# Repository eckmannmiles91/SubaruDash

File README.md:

# SubaruDash

Digital dash project for 2013 Subaru WRX

## Overview

This project documents the development of a custom digital dashboard for a 2013 WRX, including cluster EEPROM backup/modification work.

## Documentation

- [CLUSTER_EEPROM_GUIDE.md](CLUSTER_EEPROM_GUIDE.md) - Guide for reading and writing the instrument cluster EEPROM using CH341A programmer
- [CAN_SNIFFING_GUIDE.md](CAN_SNIFFING_GUIDE.md) - Guide for CAN bus sniffing using Raspberry Pi 5 and MCP2515 module
- [CUSTOM_PCB_DESIGN.md](CUSTOM_PCB_DESIGN.md) - Custom "WRX Power & CAN HAT" PCB design specification

## Tools

- [tools/AsProgrammer/](tools/AsProgrammer/) - AsProgrammer v2.1.2 for reading/writing EEPROM chips (Windows)

## Hardware

### Cluster EEPROM Work
- CH341A USB EEPROM Programmer - [Amazon Link](https://www.amazon.com/dp/B07VNVVXW6)
- 2013 WRX backup instrument cluster (eBay)

### CAN Bus Sniffing
- Raspberry Pi 5 with OpenDash installed
- 2x MCP2515 CAN Bus Module (TJA1050 transceiver)
- OBD-II Splitter Cable
- 12V to 5V buck converter
- Jumper wires

## Current Status

### Cluster EEPROM Work
- [ ] Backup cluster received (ordered from eBay)
- [x] EEPROM chip identified (S93C76)
- [x] Main MCU identified (MB90428GAV)
- [x] CH341A programmer purchased and set up
- [x] Documentation created for EEPROM reading/writing
- [ ] Backup cluster EEPROM read and backed up

### CAN Bus Sniffing
- [x] MCP2515 CAN modules available (2x)
- [x] Raspberry Pi 5 with OpenDash running
- [x] OBD-II splitter cable available
- [x] CAN sniffing documentation created
- [ ] MCP2515 connected to Pi5 GPIO
- [ ] SocketCAN configured on Pi5
- [ ] CAN bus data collection started
- [ ] CAN IDs mapped for WRX sensors

### Digital Dash Development
- [ ] Hardware platform selection
- [ ] Display selection
- [ ] Software architecture design
- [ ] Implementation

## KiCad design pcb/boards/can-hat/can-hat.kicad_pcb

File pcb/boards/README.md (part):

# SubaruDash Split Board Schematics

This directory contains the split schematics from the combined `wrx-power-can-hat-MANUAL.kicad_sch` into three separate stackable Raspberry Pi HAT boards.

## Board Structure

### 1. Power HAT (`power-hat/`)
**Schematic Status: ✅ ERC CLEAN - 0 Errors, 55 Warnings**
**PCB Status: 🟡 Layout v6 Ready - J1 updated to Micro-Fit 3.0 6-pin**

Core power management and ignition control:
- **U1**: TPS54560 5V/5A Buck Converter (12V → 5V)
- **U3**: ATtiny85 Power Management MCU
- **J1**: 12V Input Molex Micro-Fit 3.0 (6-pin)
- **J2**: 40-pin Raspberry Pi GPIO Header
- **J4**: 4-pin PWM Fan Connector (30mm fan)
- **F1**: Input Fuse
- MOSFETs (Q1, Q2, Q3) for power switching
- Ignition detection optocoupler circuit

**Connected Signals via Pi Header:** (see [GPIO_ALLOCATION.md](GPIO_ALLOCATION.md))
- +5V (pins 2, 4)
- +3.3V (pins 1, 17)
- GND (pins 6, 9, 14, 20, 25, 30, 34, 39)
- SHUTDOWN_REQ (pin 7/GPIO4) - Pi → ATtiny85 shutdown request
- HEARTBEAT_LED (pin 11/GPIO17) - ATtiny85 → Pi heartbeat status
- TIMER_LED (pin 13/GPIO27) - ATtiny85 → Pi timer status
- IGN_DETECT (pin 15/GPIO22) - Optocoupler → Pi ignition state
- FAN_PWM (pin 32/GPIO12) - Pi → Fan PWM speed control
- FAN_TACH (pin 33/GPIO13) - Fan → Pi tachometer feedback

**PCB Layout Features:**
- Board outline: 65mm × 56mm (standard Pi HAT)
- 4× M2.5 HAT mounting holes at corners (3.5, 3.5), (61.5, 3.5), (3.5, 52.5), (61.5, 52.5)
- 4× M3 fan mounting holes for 30mm fan (24mm spacing) centered at (32.5, 32)
- 40-pin GPIO header (J2) horizontal along top edge
- Power section (U1, L1) on left side, clear of fan zone
- MCU section (U3, Y1) on right side
- Power switching (Q1) bottom-right
- Layout scripts: `layout_power_hat_v5.py` (optimized), `layout_power_hat_v6.py` (DRC-compliant)

**Two-Layer Component Strategy:**
- **Front layer (F.Cu):** Through-hole and thermal components
  - Connectors: J1, J2, J3, J4, JP1, JP2
  - ICs: U1 (TPS54560), U2 (optocoupler), U3 (ATtiny85)
  - Power: Q1 (TO-220 MOSFET), L1 (inductor), F1 (fuse)
  - Crystal: Y1
- **Back layer (B.Cu):** SMD passives positioned under related front components
  - Under U1 (buck converter): R1, R2, R_RT1, R_COMP1, D2
  - Under U3 (MCU): R4, R5, R6, R7
  - Under U2 (optocoupler): R8, R9
  - Under Q1 (MOSFET): Q2, Q3, R10
  - Under J1 (power input): D1
  - Capacitors: C1-C9, C_BOOT1, C_COMP1

### 2. CAN HAT (`can-hat/`)
**Schematic Status: ✅ ERC CLEAN - Fixed crystal, OBD-II, and power connections**
**PCB Status: ⏳ Not Started**

CAN bus communication interface:
- **U2**: MCP2515 CAN Controller (SPI interface)
- **U3**: SN65HVD230 CAN Transceiver (3.3V native)
- **U1**: AMS1117-3.3 Voltage Regulator
- **J1**: 40-pin Raspberry Pi GPIO Header
- **J2**: OBD-II 16-pin Connector
- **J3**: CAN Screw Terminal
- **Y1**: 8MHz Crystal

**Connected Signals via Pi Header:** (see [GPIO_ALLOCATION.md](GPIO_ALLOCATION.md))
- +5V (pins 2, 4) - power input (stacking or USB-C)
- +3.3V (pins 1, 17) - from AMS1117
- GND (pins 6, 9, 14, 20, 25, 30, 34, 39)
- SPI_MOSI (pin 19/GPIO10)
- SPI_MISO (pin 21/GPIO9)
- SPI_SCLK (pin 23/GPIO11)
- SPI_CE0 (pin 24/GPIO8)
- CAN_INT (pin 22/GPIO25)

**USB-C Power Input (Manual Addition Required):**
- J5: USB-C connector for bench testing
- D1, D2: SS34 Schottky diodes (power OR'ing)
- Allows power from either GPIO header or USB-C

### 3. DAC/Amp HAT (`dac-amp/`)
**Schematic Status: ✅ ERC CLEAN - 34 Errors (J7 GPIO only), 85 Warnings**
**PCB Status: ✅ READY FOR PCBA - DRC clean, Gerbers generated**

4-channel 50W Class D audio amplifier:
- **U1**: PCM5142 Stereo I2S DAC
- **U2**: AMS1117-3.3 LDO (3.3V for DAC)
- **U3**: TPA3116D2DAD Class D Amplifier (Front L/R, 50W stereo BTL)
- **U4**: TPA3116D2DAD Class D Amplifier (Rear L/R, 50W stereo BTL)
- **J3**: 4-pin 3.5mm screw terminal (Front speakers: FL+, FL-, FR+, FR-)
- **J4**: 4-pin 3.5mm screw terminal (Rear speakers: RL+, RL-, RR+, RR-)
- **J7**: 40-pin Raspberry Pi GPIO Header

**Support Components Added:**
- R1, R2: 4.7kΩ I2C pull-ups (SCL, SDA to +3.3V)
- C4-C6: PCM5142 decoupling (100nF DVDD, 100nF+10µF AVDD)
- C7-C10: TPA3116D2 bootstrap caps (100nF each, BSPx↔BSNx)
- C11-C20: TPA3116D2 PVCC decoupling (8× 100nF + 2× 10µF)
- C21-C22: TPA3116D2 GVDD decoupling (100nF each)
- C23-C30: Input coupling caps (1µF each, AC coupling to amp inputs)
- C31: 12V input bulk capacitor (100µF)
- C32: 3.3V filter capacitor (100nF)

**Connected Signals via Pi Header (J7):**
- +5V (pins 2, 4) - power input
- +3.3V (pins 1, 17) - from AMS1117
- GND (pins 6, 9, 14, 20, 25, 30, 34, 39)
- I2S_BCK (pin 12/GPIO18) - I2S bit clock
- I2S_LRCK (pin 35/GPIO19) - I2S L/R clock
- I2S_DOUT (pin 40/GPIO21) - I2S data out
- I2C_SDA (pin 3/GPIO2) - PCM5142 config
- I2C_SCL (pin 5/GPIO3) - PCM5142 config

**Volume Control:** Digital via PCM5142 I2C registers (not analog PLIMIT)

**PCB Layout Features:**
- Board outline: 65mm × 56mm (standard Pi HAT)
- 4× M2.5 HAT mounting holes at standard positions
- 2-layer board, routed via FreeRouting auto-router
- GND copper pour on back layer for thermal dissipation
- Thermal vias under U3 and U4 (6-8 vias each)
- Widened power traces: +12V @ 1.0mm, speaker outputs @ 0.75mm
- 3× fiducials for pick-and-place assembly
- Components on both front and back layers

**Manufacturing Recommendations:**
- Copper weight: 2oz preferred (1oz acceptable for prototypes)
- Surface finish: ENIG (for PCBA) or HASL lead-free
- Assembly: PCBA recommended (TPA3116D2 and PCM5142 are SMD with fine pitch)

## Scripts

| Script | Purpose |
|--------|---------|
| `split_schematic.py` | Initial split of combined schematic |
| `cleanup_schematics.py` | Remove cross-board labels |
| `fix_power_hat.py` | Remove CAN-specific labels from Power HAT |
| `fix_power_hat_complete.py` | (v1) Wire J2 pins - had position errors |
| `fix_power_hat_v2.py` | (v2) Wire J2 pins with CORRECT positions |
| `fix_power_hat_v3.py` | Add PWR_FLAG symbols for power nets |
| `fix_power_hat_v4.py` | Connect J1, F1, U1 VIN, U3 VCC |
| `fix_power_hat_v5.py` | Connect remaining components (Q1, R5-R10, Y1, J3, JP1-2) |
| `fix_power_hat_v6.py` | Final fixes: PWR_FLAG for U1, R6/Y1/R10/Q3 connections |
| `fix_power_hat_v7.py` | Restore R6 connections (12V_IGN, GND) after cleanup |
| `fix_power_hat_v8.py` | Fix Y1 Pin 1 -> XTAL1 connection |
| `fix_power_hat_v9.py` | Bridge wire for Y1 Pin 1 gap |
| `fix_power_hat_v10.py` | T-junction approach for Y1 |
| `fix_power_hat_v11.py` | Stub wire at Y1 Pin 1 (+ manual snap to pin) |
| `fix_power_hat_v12.py` | Remove orphan HEARTBEAT_LED/TIMER_LED labels |
| `fix_power_hat_v13.py` | Add no_connect for U3 pins 5,6 (superseded by v14) |
| `fix_power_hat_v14.py` | Wire U3 PB0/PB1 to GPIO17/GPIO27 for status signals |
| `fix_can_hat.py` | Complete CAN HAT wiring (GPIO, SPI, CAN, power) |
| `create_dac_amp_schematic.py` | Generate DAC/Amp schematic from scratch |
| `layout_power_hat.py` | Power HAT PCB component placement |
| `layout_power_hat_v2.py` | Improved layout with better spacing |
| `layout_power_hat_v3.py` | X735-style layout with 30mm fan |
| `fix_power_hat_fan.py` | Upgrade J4 from 2-pin to 4-pin fan connector |
| `fix_power_hat_fan_complete.py` | Wire J4 pins 3,4 to GPIO12,13 for PWM fan control |
| `layout_power_hat_v4.py` | Improved layout with fan clearance zones |
| `move_caps_to_back.py` | Move capacitors to B.Cu (back layer) |
| `fix_cap_pads.py` | Fix SMD pad layers for back-layer components |
| `move_smd_to_back.py` | Move resistors, diodes, SOT-23 MOSFETs to B.Cu |
| `fix_back_positions.py` | Apply board offset to back-layer component positions |
| `fix_boot_comp_caps.py` | Move C_BOOT1/C_COMP1 to B.Cu (back layer) |
| `layout_power_hat_v5.py` | Optimized layout with all components positioned |
| `layout_power_hat_v6.py` | DRC-compliant spacing, J1 Micro-Fit 3.0 support |

## Current ERC Status

### Power HAT
After running fix scripts v2 through v5:
- ✅ J2 Pi header 40 pins connected (v2)
- ✅ PWR_FLAG symbols added for +5V, +3.3V, GND (v3)
- ✅ J1 12V input connector connected (v4)
- ✅ F1 fuse output -> 12V_FUSED (v4)
- ✅ U1 VIN -> 12V_FUSED (v4)
- ✅ U3 VCC -> +5V (v4)
- ✅ TPS54560 compensation network (C_COMP1, R_RT1) (v5)
- ✅ Power switching circuit (Q1, R5, R6, R8) (v5)
- ✅ Crystal oscillator Y1 -> XTAL1/XTAL2 (v5)
- ✅ J3, JP1, JP2 headers marked as no-connect (v5)
- ✅ R10 LED resistor -> GND (v5)
- ✅ J4 fan connector -> FAN+ (v5)
- ✅ PWR_FLAG on 12V_FUSED net (v6) - fixes U1 VIN power error
- ✅ R6 Pin 1 -> 12V_IGN (v6)
- ✅ Y1 Pin 1 -> XTAL1 (v6)
- ✅ Q3 Gate -> FAN_PWM (v6)
- ✅ R6 Pin 1 -> 12V_IGN, Pin 2 -> GND restored (v7)
- ✅ Y1 Pin 1 -> XTAL1 (v8-v11 + manual fix)
- ✅ Orphan labels deleted manually
- ✅ U3 PB0 (HEARTBEAT_LED) -> J2 Pin 11 (GPIO17) (v14)
- ✅ U3 PB1 (TIMER_LED) -> J2 Pin 13 (GPIO27) (v14)
- ✅ J1 updated to Molex Micro-Fit 3.0 6-pin (manual)
- ✅ C6 fixed: bottom pin changed from +3.3V to GND (was shorted)
- ✅ C8 reconnected as feedforward cap: +5V to U1-FB (was incorrectly on XTAL2)
- ✅ C9 label fixed: 12V_FUSED (was 12V_IGN)
- ✅ R6 label fixed: 12V_IGN to GND (ignition detection divider)
- ✅ D1 (TVS) moved away from J2, reconnected: 12V_FUSED to GND
- ✅ Removed stray 12V_IGN label hidden behind U1
- ✅ PWR_FLAG added to 12V_FUSED and +3.3V nets
- ✅ **ERC: 0 ERRORS, 55 WARNINGS** (warnings are non-critical)

### CAN HAT
After running fix_can_hat.py:
- ✅ J1 Pi header 40 pins connected with labels
- ✅ SPI bus: MOSI, MISO, SCLK, CE0 to MCP2515
- ✅ CAN_INT from MCP2515 to GPIO25
- ✅ MCP2515 to SN65HVD230 (CAN_TX, CAN_RX)
- ✅ Crystal Y1 connected (XTAL1, XTAL2)
- ✅ CAN bus to J2 (OBD-II) pins 6, 14
- ✅ CAN bus to J3 (screw terminal)
- ✅ Power distribution (AMS1117 5V_BUS -> +3.3V)
- ✅ PWR_FLAG symbols for +5V, +3.3V, GND
- ✅ Unused GPIO pins marked no-connect
- ✅ Unused OBD-II pins marked no-connect
- ⏳ USB-C power circuit components need manual addition
- ⚠️ Run ERC in KiCad to check remaining errors

### DAC/Amp
After manual wiring in KiCad:
- ✅ I2C pull-ups (R1, R2) wired to +3.3V and I2C_SCL/SDA labels
- ✅ PCM5142 decoupling (C4-C6) wired to +3.3V and GND
- ✅ Bootstrap caps (C7-C10) wired BSPx↔BSNx (NOT to outputs)
- ✅ PVCC decoupling (C11-C20) wired to +12V and GND
- ✅ GVDD decoupling (C21-C22) wired with PWR_FLAG (internal 5.2V)
- ✅ Input coupling (C23-C30) wired in series with amp inputs
- ✅ Power filtering (C31, C32) wired to +12V/+3.3V and GND
- ✅ Speaker outputs (J3, J4) wired to U3/U4 OUTP/OUTN pins
- ✅ PWR_FLAG added to +12V and GND nets
- ✅ **ERC: 34 ERRORS (all J7 GPIO unconnected - expected), 85 WARNINGS**

## GPIO Pin Allocation

See **[GPIO_ALLOCATION.md](GPIO_ALLOCATION.md)** for the complete GPIO pin mapping across all three HAT boards. This document tracks:
- Which GPIO pins are used by each board
- Signal directions and descriptions
- Available GPIOs for future expansion

## Technical Notes

### Conn_02x20_Odd_Even Pin Positions
The Raspberry Pi GPIO header uses specific pin offsets:
- **Odd pins (left)**: x = symbol_x - 5.08mm
- **Even pins (right)**: x = symbol_x + 7.62mm
- **Y spacing**: 2.54mm per row, starting at y_offset = 22.86mm

For J2 at position (200, 150):
- Pin 1: (194.92, 127.14)
- Pin 2: (207.62, 127.14)
- Pin 3: (194.92, 129.68)
- etc.

### Power Flow
```
12V_IGN (vehicle) → F1 (fuse) → 12V_FUSED
                                    ↓
                               U1 TPS54560
                                    ↓
                                  +5V → Pi Header, CAN HAT
                                    ↓
                               U3 LDO (on CAN HAT or Power HAT)
                                    ↓
                                 +3.3V → MCUs, DAC
```

## Next Steps

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
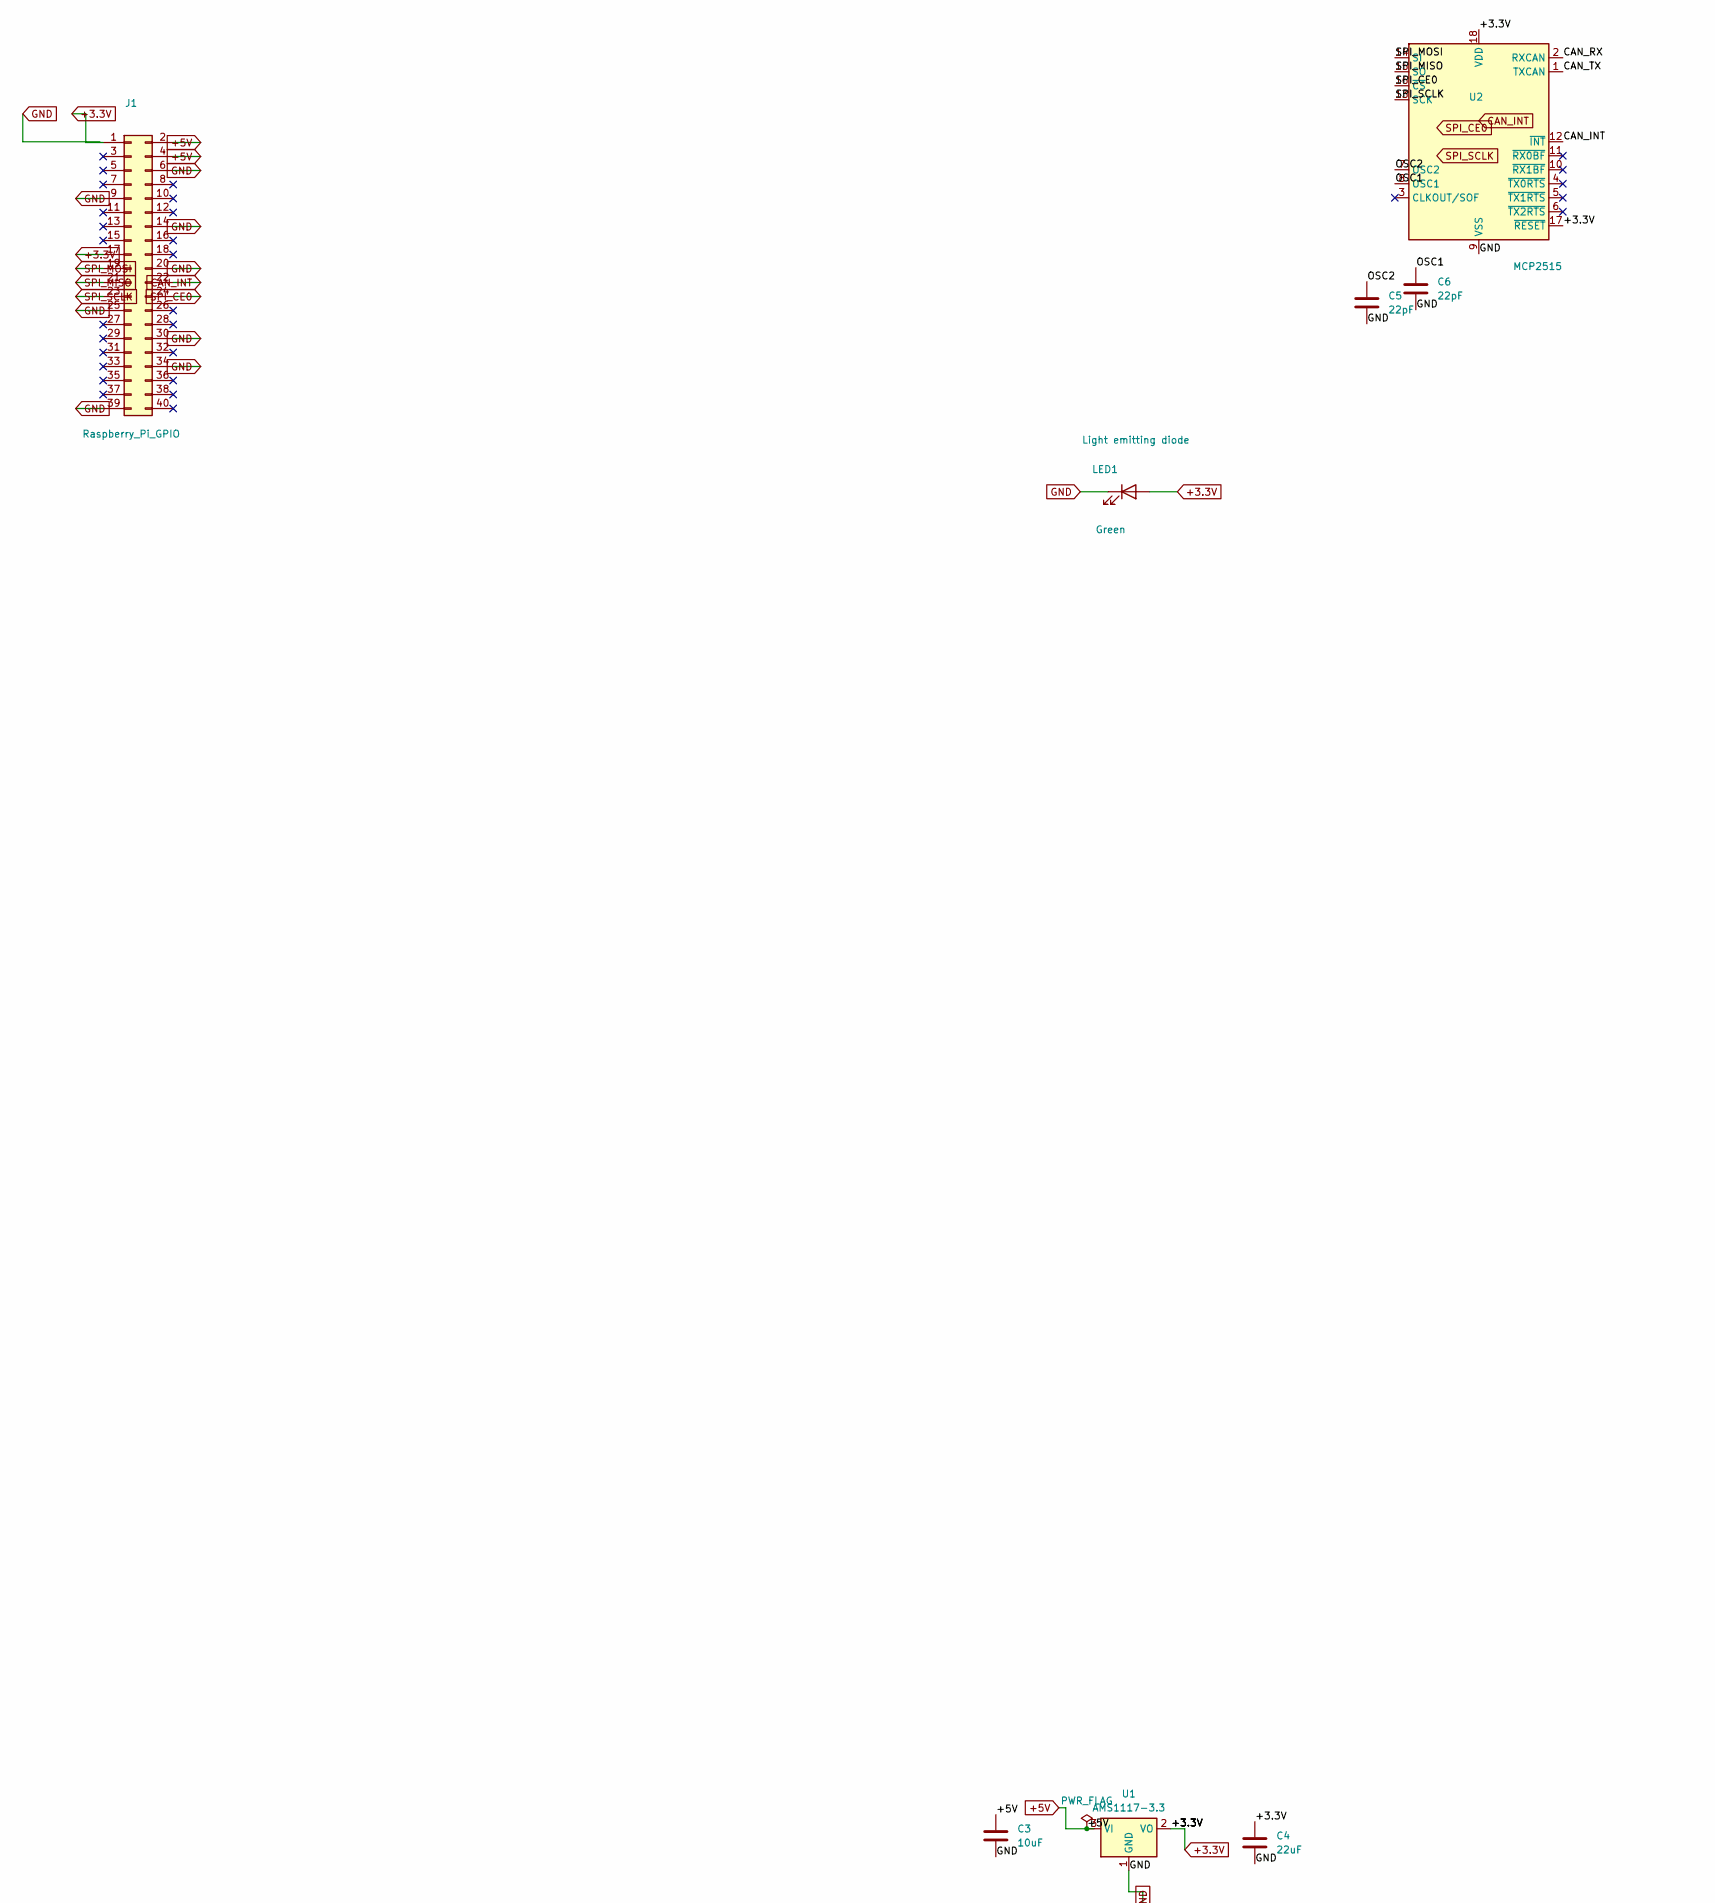
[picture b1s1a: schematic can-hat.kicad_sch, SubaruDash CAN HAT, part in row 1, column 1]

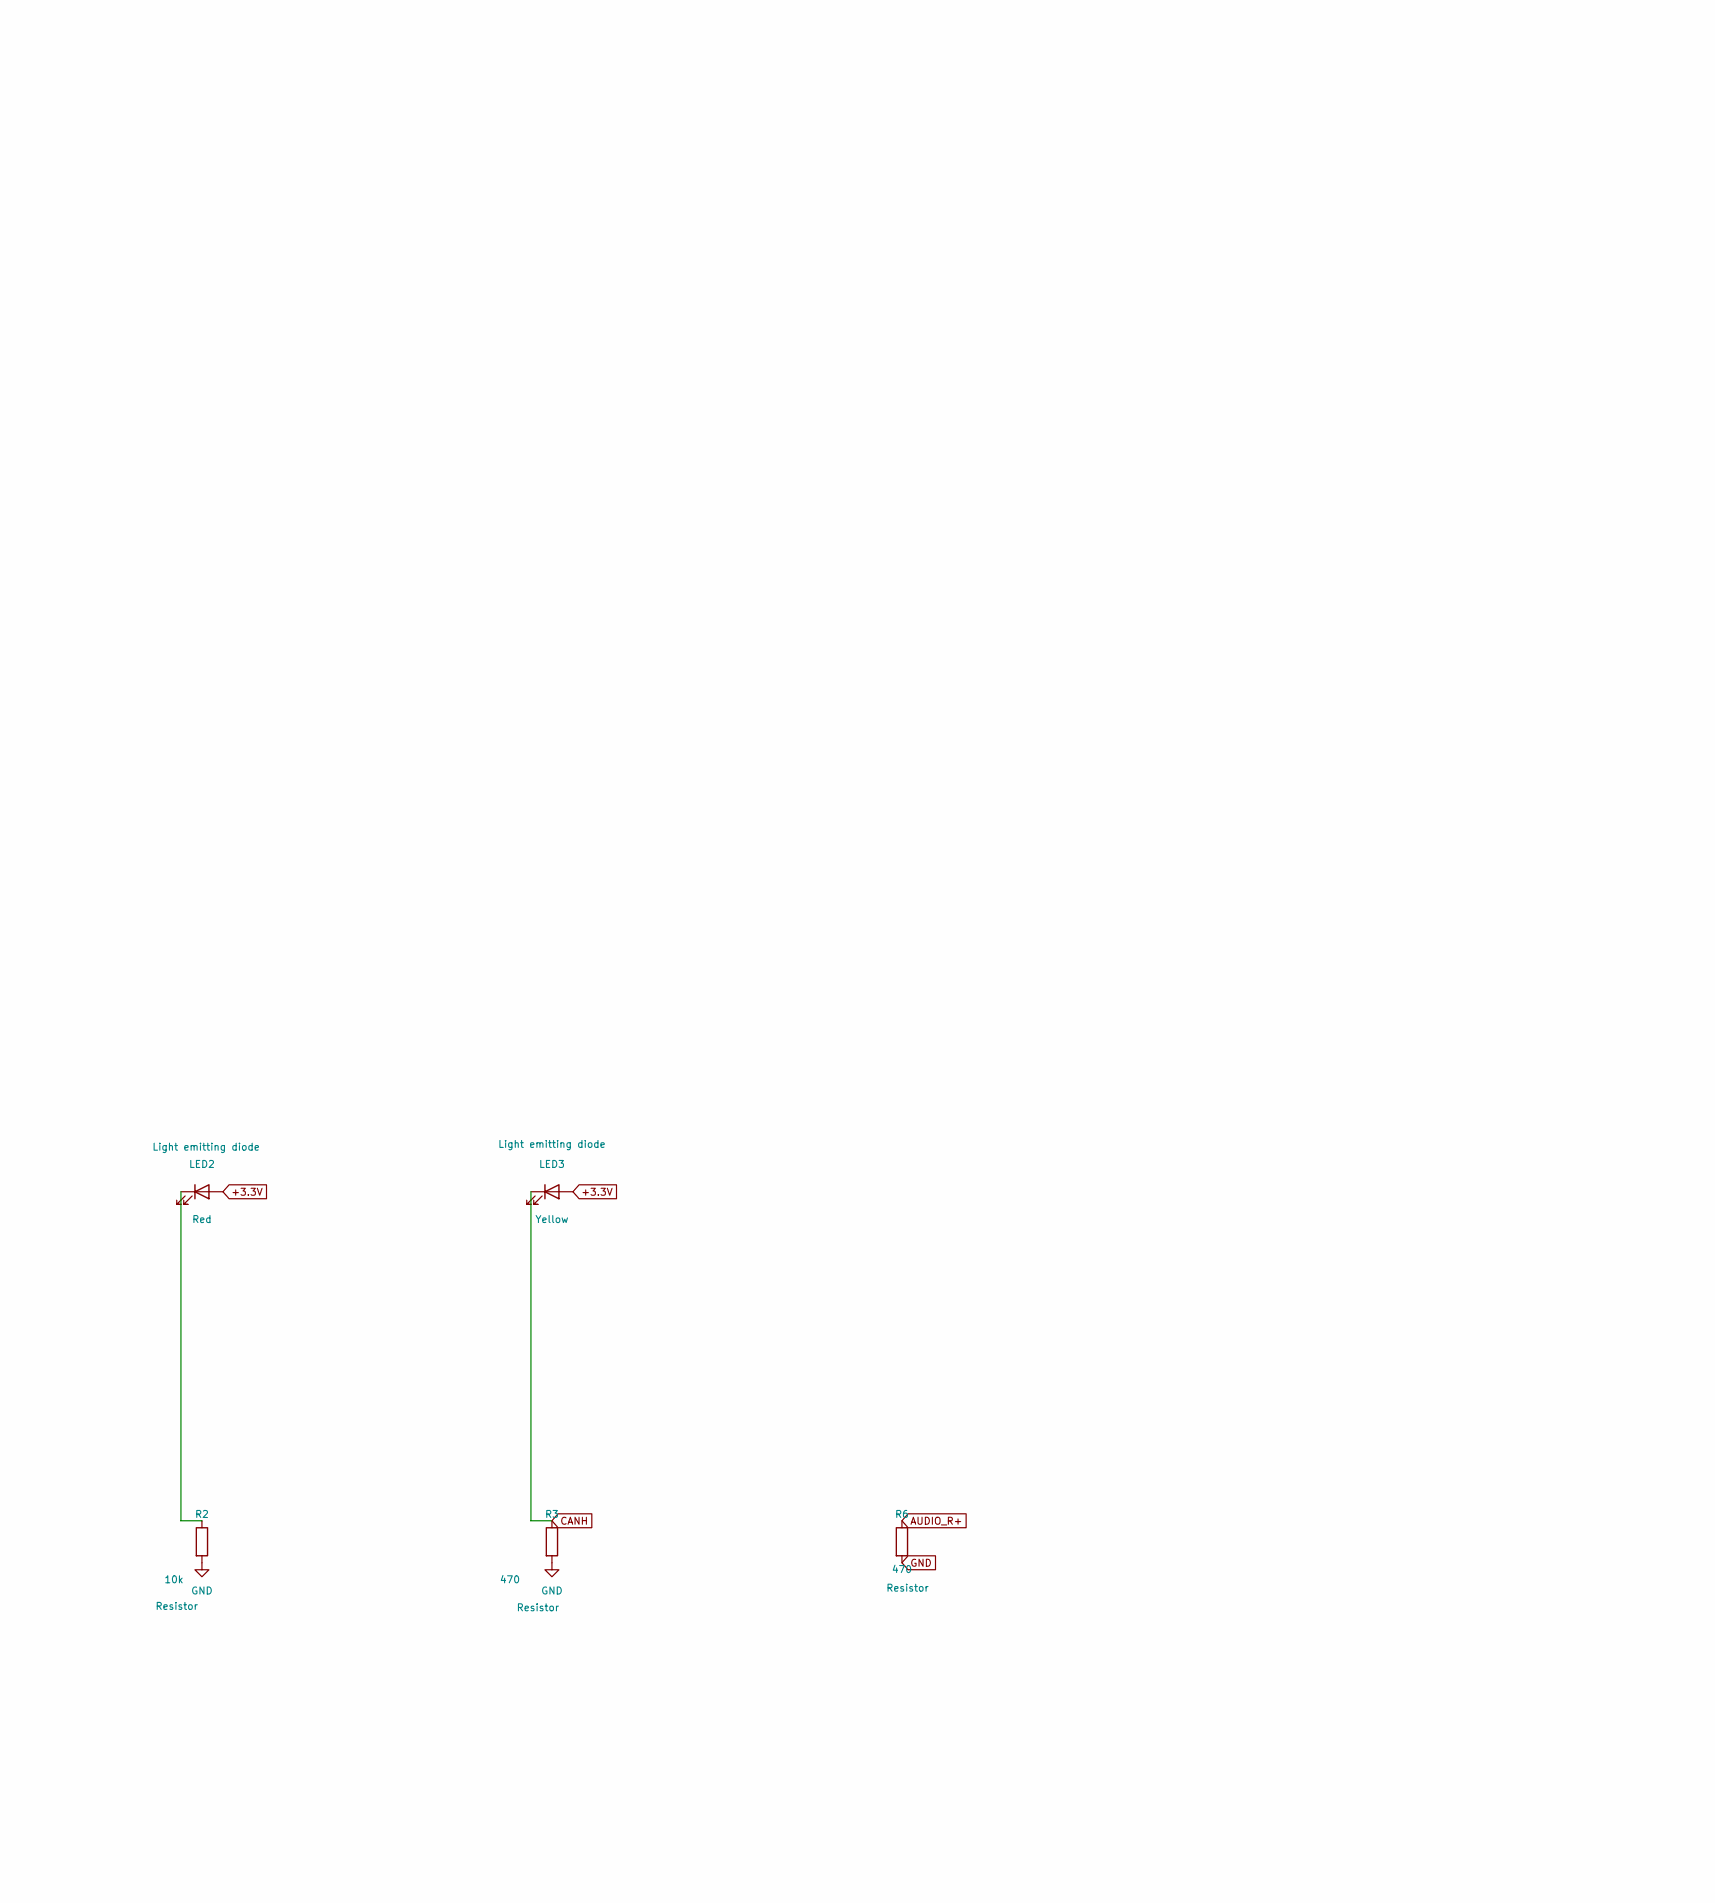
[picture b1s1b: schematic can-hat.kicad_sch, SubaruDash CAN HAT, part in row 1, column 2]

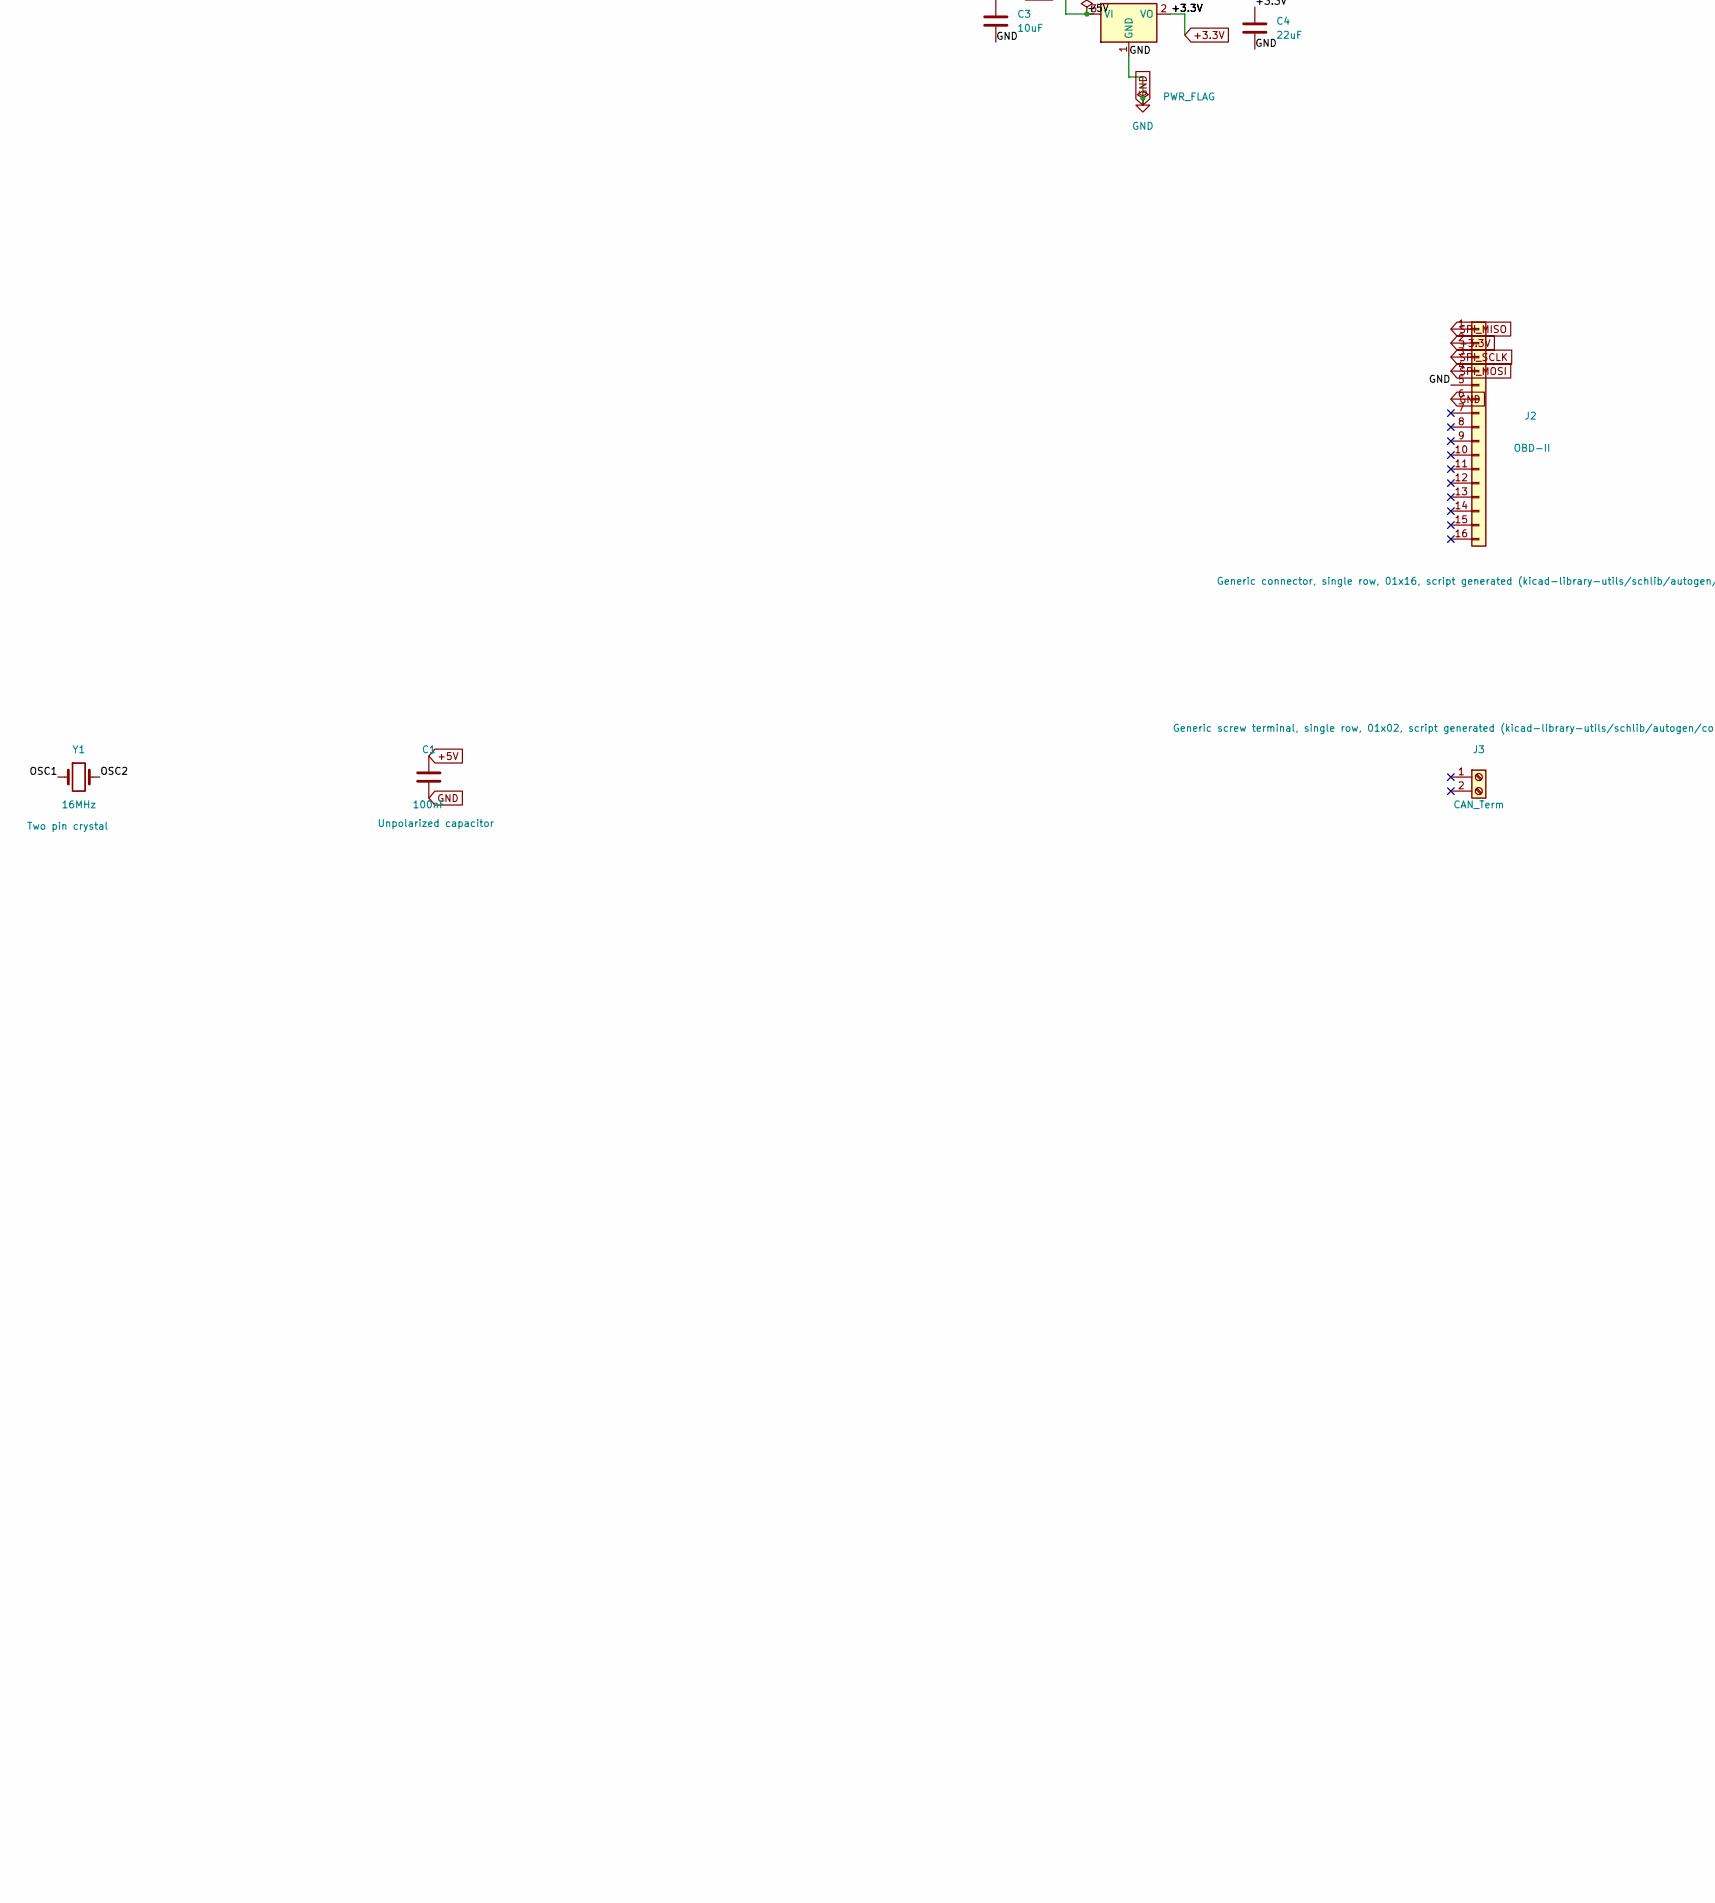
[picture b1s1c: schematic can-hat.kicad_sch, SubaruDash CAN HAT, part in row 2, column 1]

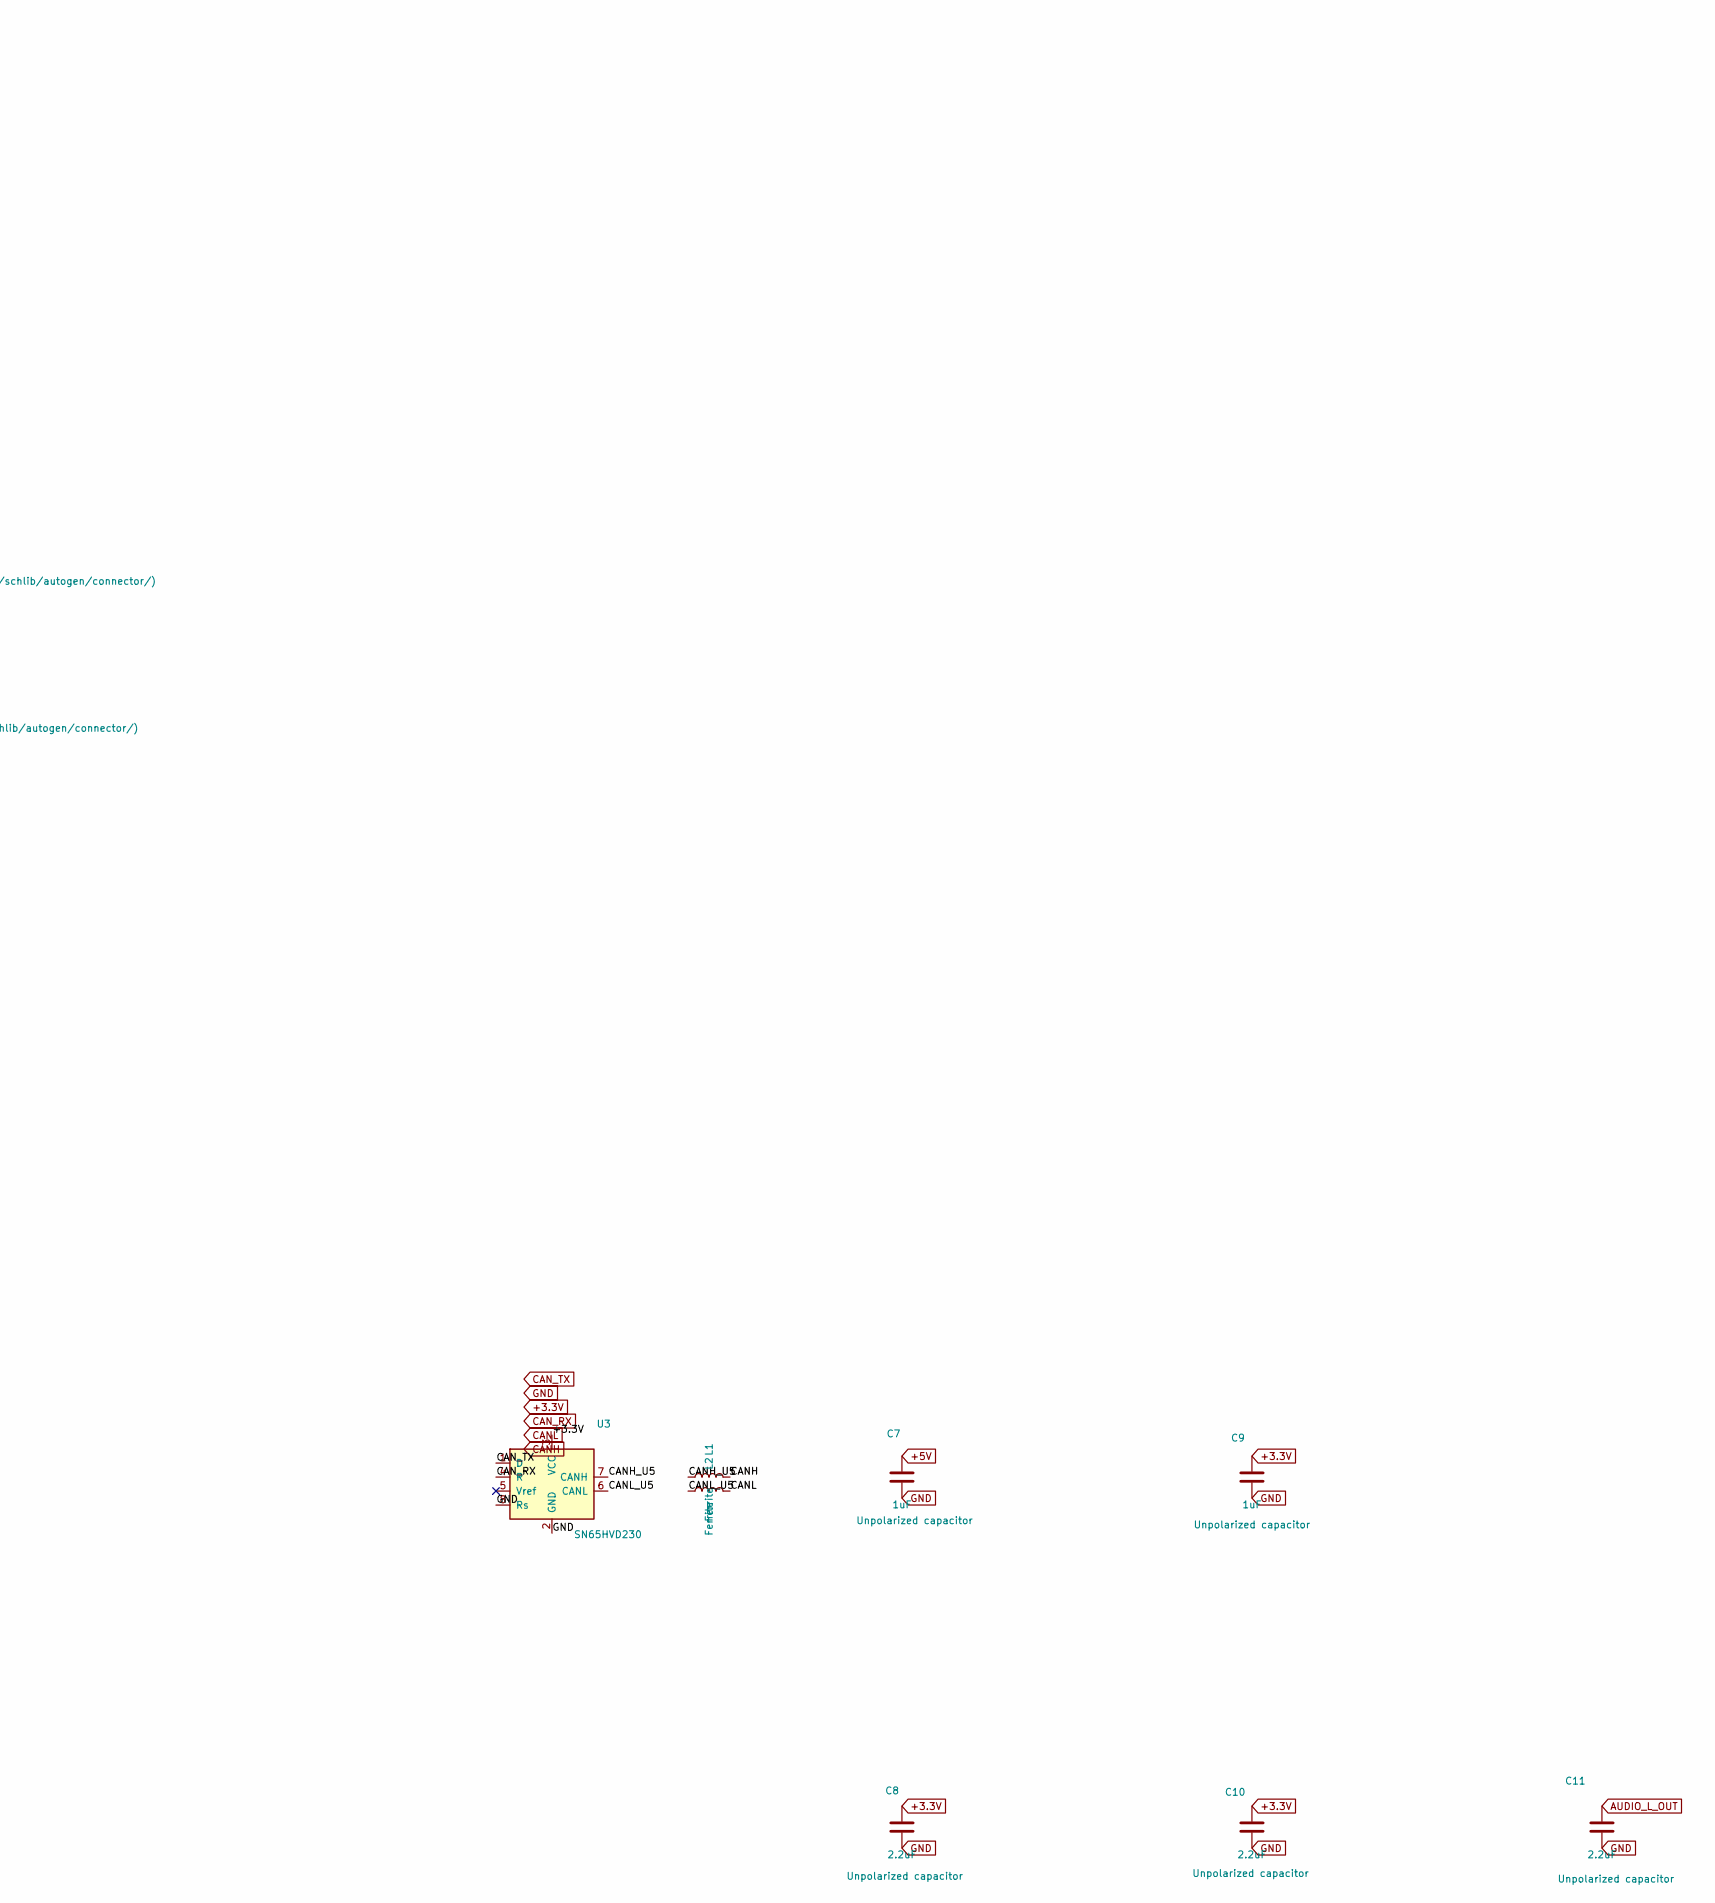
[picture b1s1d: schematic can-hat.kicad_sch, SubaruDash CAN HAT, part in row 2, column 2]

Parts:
C1: 100nF; C_0805_2012Metric
C3: 10uF; C_1206_3216Metric
C4: 22uF; C_1206_3216Metric
C5, C6: 22pF; C_0805_2012Metric
C7, C9: 1uF; C_0805_2012Metric
C8, C10, C11: 2.2uF; C_0805_2012Metric
J1: Raspberry_Pi_GPIO; PinHeader_2x20_P2.54mm_Vertical
J2: OBD-II; PinHeader_2x08_P2.54mm_Vertical
J3: CAN_Term; TerminalBlock_Phoenix_MKDS-1,5-2-5.08_1x02_P5.08mm_Horizont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
L1, L2: Ferrite; L_0805_2012Metric
LED1: Green; LED_0805_2012Metric
LED2: Red; LED_0805_2012Metric
LED3: Yellow; LED_0805_2012Metric
R2: 10k; R_0805_2012Metric
R3, R6: 470; R_0805_2012Metric
U1: AMS1117-3.3; SOT-223-3_TabPin2
U2: MCP2515; SOIC-18W_7.5x11.6mm_P1.27mm
U3: SN65HVD230; SOIC-8_3.9x4.9mm_P1.27mm
Y1: 16MHz; Crystal_HC49-4H_Vertical

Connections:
+3.3V: C4.1, C8.1, C9.1, C10.1, J1.1, J1.17, J2.2, LED1.2 (A), LED2.2 (A), LED3.2 (A), U1.2 (VO), U2.17 (~RESET), U2.18 (VDD), U3.3 (VCC)
+5V: C1.1, C3.1, C7.1, J1.2, J1.4, U1.3 (VI)
/CANH_U5: L1.1, U3.7 (CANH)
/CANL_U5: L2.1, U3.6 (CANL)
/OSC1: C6.1, U2.8 (OSC1), Y1.1
/OSC2: C5.1, U2.7 (OSC2), Y1.2
AUDIO_L_OUT: C11.1
AUDIO_R+: R6.1
CANH: L1.2, LED3.1 (K), R3.1
CANL: L2.2
CAN_INT: J1.22, U2.12 (~INT)
CAN_RX: U2.2 (RXCAN), U3.4 (R)
CAN_TX: U2.1 (TXCAN), U3.1 (D)
GND: C1.2, C3.2, C4.2, C5.2, C6.2, C7.2, C8.2, C9.2, C10.2, C11.2, J1.6, J1.9, J1.14, J1.20, J1.25, J1.30, J1.34, J1.39, J2.5, J2.6, LED1.1 (K), R2.2, R3.2, R6.2, U1.1 (GND), U2.9 (VSS), U3.2 (GND), U3.8 (Rs)
unnamed: LED2.1 (K), R2.1
SPI_CE0: J1.24, U2.16 (~CS)
SPI_MISO: J1.21, J2.1, U2.15 (SO)
SPI_MOSI: J1.19, J2.4, U2.14 (SI)
SPI_SCLK: J1.23, J2.3, U2.13 (SCK)

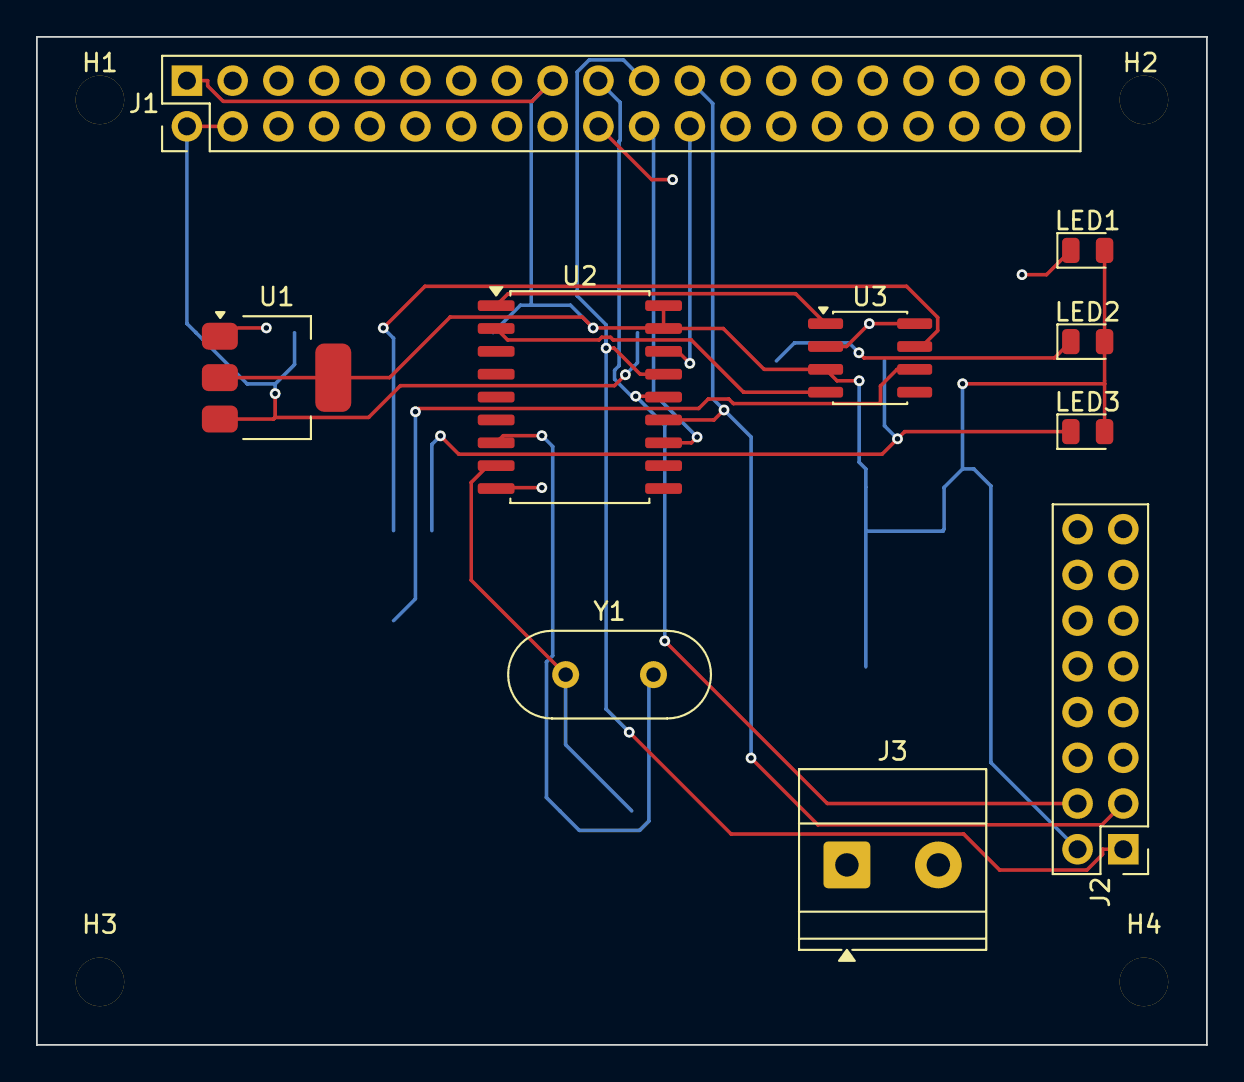
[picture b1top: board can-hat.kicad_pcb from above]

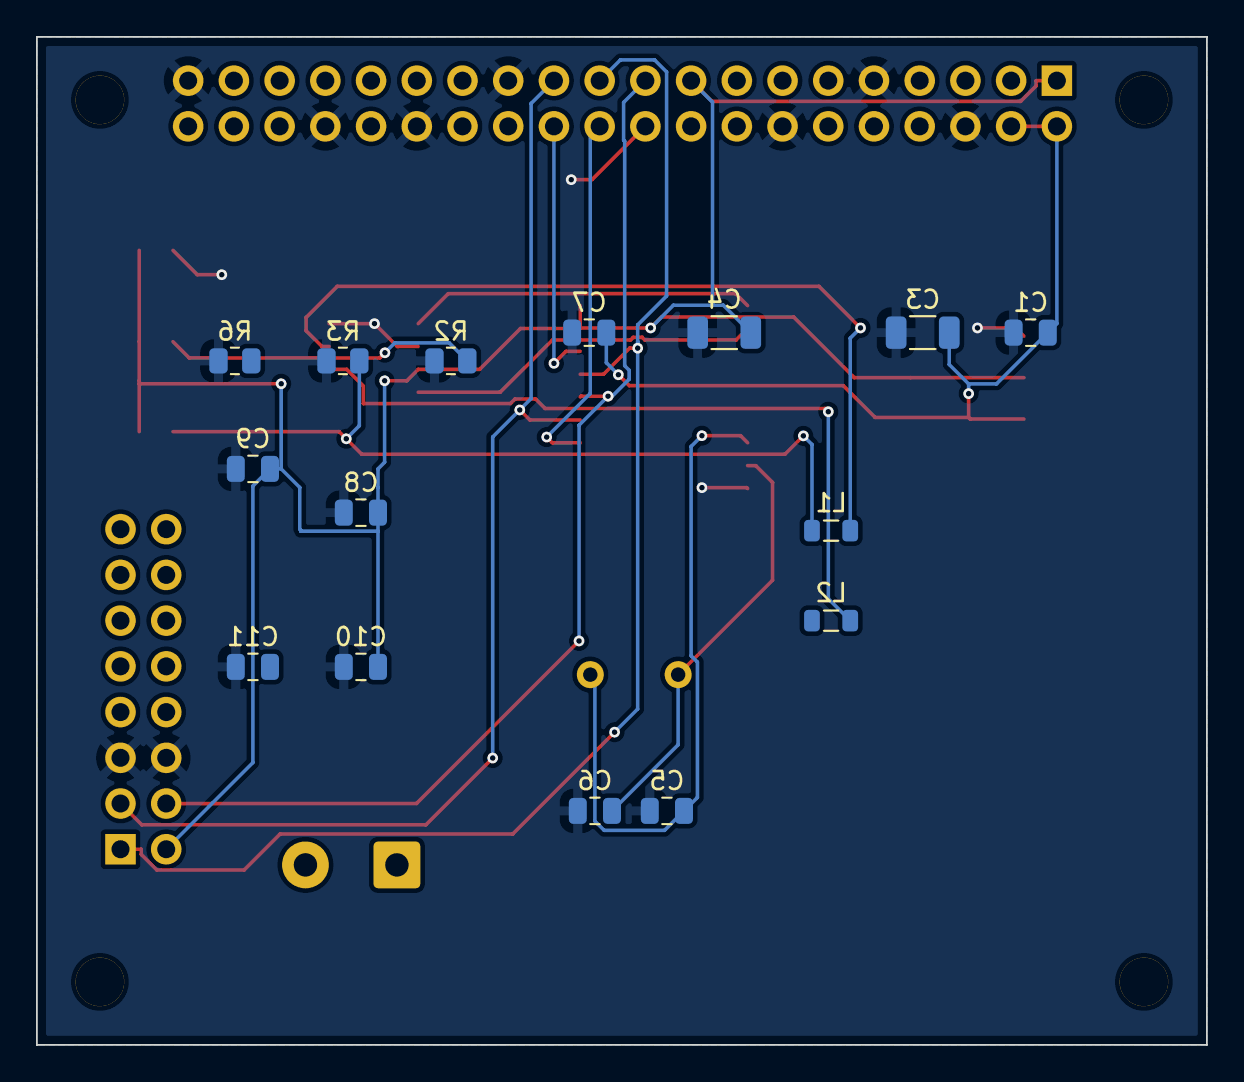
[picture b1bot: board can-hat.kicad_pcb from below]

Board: 2 copper layers, 65.0 x 56.0 mm, 29 parts (15 on the bottom side), 16 nets.

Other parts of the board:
H1, H2, H3, H4: MountingHole; MountingHole_2.7mm_M2.5

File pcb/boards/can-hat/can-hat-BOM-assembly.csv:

Designator,Quantity,Value,Footprint,MPN,Manufacturer,Description
U3,1,SN65HVD230,SOIC-8_3.9x4.9mm_P1.27mm,SN65HVD230DR,Texas Instruments,CAN Transceiver 3.3V
U2,1,MCP2515,SOIC-18W_7.5x11.6mm_P1.27mm,MCP2515-I/SO,Microchip,CAN Controller SPI
U1,1,AMS1117-3.3,SOT-223-3_TabPin2,AMS1117-3.3,Advanced Monolithic Systems,3.3V LDO Regulator
Y1,1,16MHz,Crystal_HC49-4H_Vertical,FOXSLF/160-20,FOX Electronics,16MHz Crystal HC49
C5,1,22pF,C_0805_2012Metric,CL21C220JBANNNC,Samsung,22pF 50V C0G 0805
C6,1,22pF,C_0805_2012Metric,CL21C220JBANNNC,Samsung,22pF 50V C0G 0805
C1,1,100nF,C_0805_2012Metric,CL21B104KBCNNNC,Samsung,100nF 50V X7R 0805
C7,1,1uF,C_0805_2012Metric,CL21B105KAFNNNE,Samsung,1uF 25V X7R 0805
C9,1,1uF,C_0805_2012Metric,CL21B105KAFNNNE,Samsung,1uF 25V X7R 0805
C8,1,2.2uF,C_0805_2012Metric,CL21B225KOFNNNE,Samsung,2.2uF 16V X7R 0805
C10,1,2.2uF,C_0805_2012Metric,CL21B225KOFNNNE,Samsung,2.2uF 16V X7R 0805
C11,1,2.2uF,C_0805_2012Metric,CL21B225KOFNNNE,Samsung,2.2uF 16V X7R 0805
C3,1,10uF,C_1206_3216Metric,CL31B106KAHNNNE,Samsung,10uF 25V X5R 1206
C4,1,22uF,C_1206_3216Metric,CL31A226KAHNNNE,Samsung,22uF 25V X5R 1206
R2,1,10k,R_0805_2012Metric,RC0805FR-0710KL,Yageo,10k 1% 0805
R3,1,470,R_0805_2012Metric,RC0805FR-07470RL,Yageo,470 ohm 1% 0805
R6,1,470,R_0805_2012Metric,RC0805FR-07470RL,Yageo,470 ohm 1% 0805
L1,1,Ferrite,L_0805_2012Metric,BLM21PG221SN1D,Murata,Ferrite Bead 220 ohm 0805
L2,1,Ferrite,L_0805_2012Metric,BLM21PG221SN1D,Murata,Ferrite Bead 220 ohm 0805
LED1,1,Green,LED_0805_2012Metric,150080VS75000,Wurth,Green LED 0805
LED2,1,Red,LED_0805_2012Metric,150080RS75000,Wurth,Red LED 0805
LED3,1,Yellow,LED_0805_2012Metric,150080YS75000,Wurth,Yellow LED 0805
J1,1,Raspberry_Pi_GPIO,PinHeader_2x20_P2.54mm_Vertical,PH2-40-UA,Adam Tech,2x20 Pin Header 2.54mm
J2,1,OBD-II,PinHeader_2x08_P2.54mm_Vertical,PH2-16-UA,Adam Tech,2x8 Pin Header 2.54mm
J3,1,CAN_Term,TerminalBlock_Phoenix_MKDS-1.5-2-5.08,1729128,Phoenix Contact,2-pos Terminal Block 5.08mm
